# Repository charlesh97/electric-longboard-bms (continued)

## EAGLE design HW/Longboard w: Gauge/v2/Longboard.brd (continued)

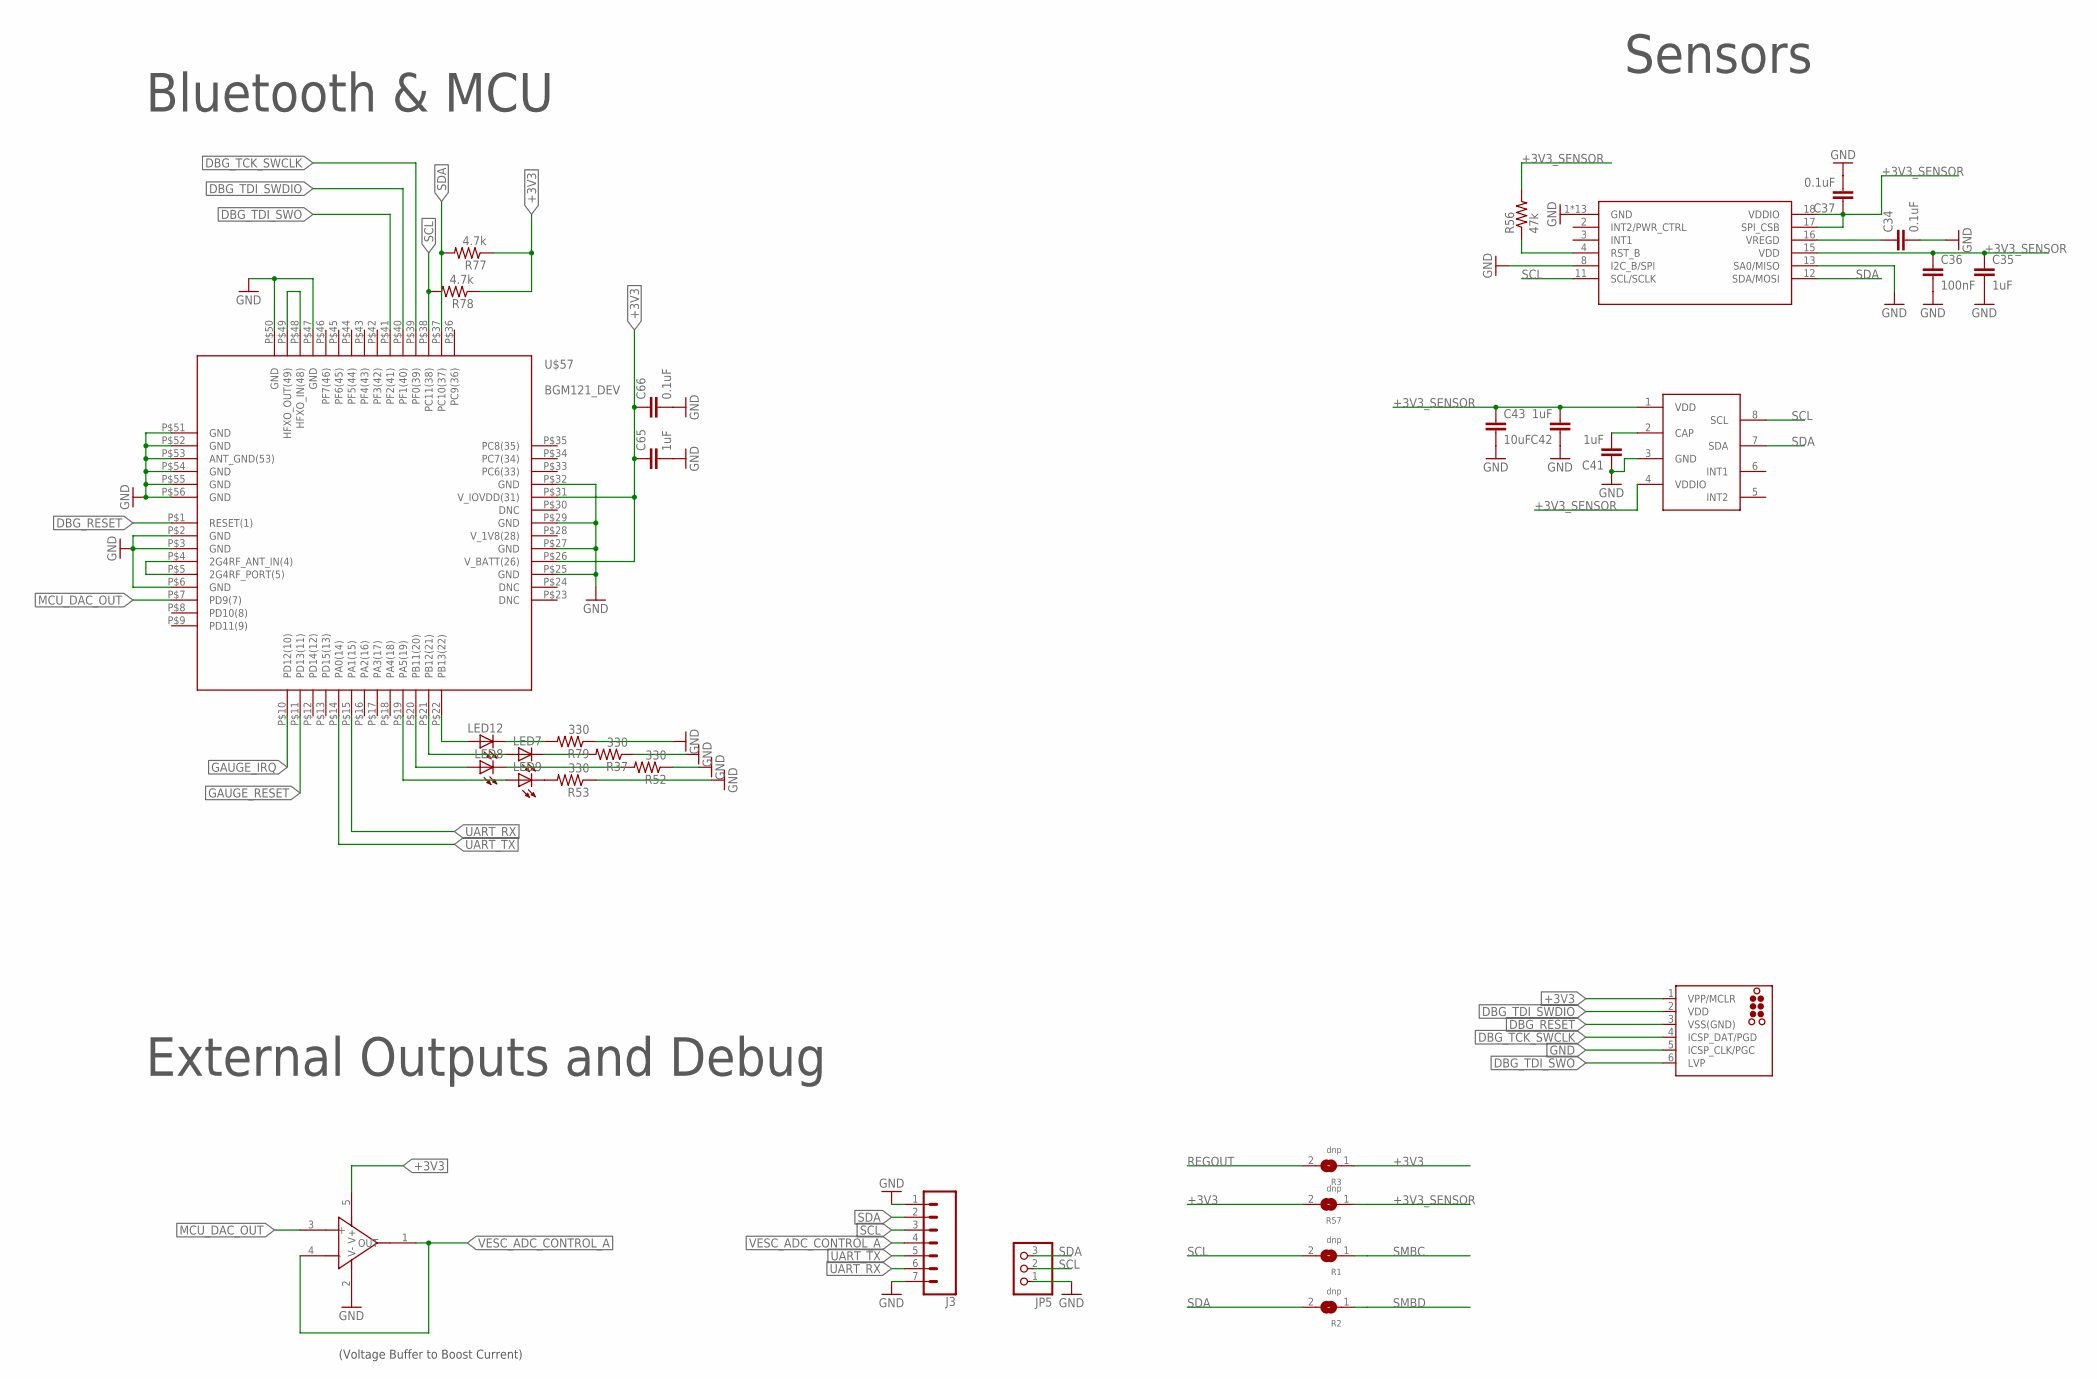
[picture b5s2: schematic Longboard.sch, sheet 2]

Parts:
C34, C37, C66: 0.1uF; C0402
C35, C41, C42, C65: 1uF; C0402
C36: 100nF; C0402
C43: 10uF; C0603
J2: TC2030-MCP-NL
J3: CONN_07; 1X07
JP5: PINHD-1X3; 1X03
LED7, LED8, LED9, LED12: LEDCHIP-LED0603; CHIP-LED0603
R1, R2, R3, R57: dnp; SOLDERJUMPER_ARROW_NOPASTE
R37, R52, R53, R79: 330; R0402
R56: 47k; R0402
R77, R78: 4.7k; R0402
U$5: MCP6001; SOT23-5L
U$25: MLP3115A2
U$34: FXAS21002
U$57: BGM121_DEV; BGM121_PAC

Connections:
+3V3: C65.1, C66.1, J2.1 (VPP/MCLR), R3.1, R57.2, R77.1, R78.1, U$5.5 (V+), U$57.P$26 (V_BATT(26)), U$57.P$31 (V_IOVDD(31))
+3V3_SENSOR: C35.1, C36.1, C37.1, C42.2, C43.1, R56.2, R57.1, U$25.1 (VDD), U$25.4 (VDDIO), U$34.15 (VDD), U$34.17 (SPI_CSB), U$34.18 (VDDIO)
DBG_RESET: J2.3 (VSS(GND)), U$57.P$1 (RESET(1))
DBG_TCK_SWCLK: J2.4 (ICSP_DAT/PGD), U$57.P$39 (PF0(39))
DBG_TDI_SWDIO: J2.2 (VDD), U$57.P$40 (PF1(40))
DBG_TDI_SWO: J2.6 (LVP), U$57.P$41 (PF2(41))
GAUGE_IRQ: U$57.P$10 (PD12(10)); also elsewhere on the board
GAUGE_RESET: U$57.P$11 (PD13(11)); also elsewhere on the board
GND: C34.2, C35.2, C36.2, C37.2, C41.1, C42.1, C43.2, C65.2, C66.2, J2.5 (ICSP_CLK/PGC), J3.1, J3.7, JP5.1, R37.1, R52.1, R53.1, R79.1, U$5.2 (V-), U$25.3 (GND), U$34.1 (GND), U$34.5 (GND), U$34.6 (GND), U$34.7 (GND), U$34.9 (GND), U$34.10 (GND), U$34.13 (SA0/MISO), U$34.14 (GND), U$34.19 (GND), U$34.20 (GND), U$34.21 (GND), U$34.22 (GND), U$34.23 (GND), U$34.24 (GND), U$57.P$2 (GND), U$57.P$3 (GND), U$57.P$6 (GND), U$57.P$25 (GND), U$57.P$27 (GND), U$57.P$29 (GND), U$57.P$32 (GND), U$57.P$47 (GND), U$57.P$50 (GND), U$57.P$51 (GND), U$57.P$52 (GND), U$57.P$53 (ANT_GND(53)), U$57.P$54 (GND), U$57.P$55 (GND), U$57.P$56 (GND); also elsewhere on the board
MCU_DAC_OUT: U$5.3 (+), U$57.P$7 (PD9(7))
unnamed: LED12.A, U$57.P$22 (PB13(22))
unnamed: LED7.A, U$57.P$21 (PB12(21))
unnamed: LED8.A, U$57.P$20 (PB11(20))
unnamed: LED9.A, U$57.P$19 (PA5(19))
unnamed: R56.1, U$34.4 (RST_B)
unnamed: LED7.C, R37.2
unnamed: LED8.C, R52.2
unnamed: LED9.C, R53.2
unnamed: C34.1, U$34.16 (VREGD)
unnamed: C41.2, U$25.2 (CAP)
unnamed: U$57.P$4 (2G4RF_ANT_IN(4)), U$57.P$5 (2G4RF_PORT(5))
unnamed: LED12.C, R79.2
unnamed: U$57.P$48 (HFXO_IN(48)), U$57.P$49 (HFXO_OUT(49))
REGOUT: R3.2; also elsewhere on the board
SCL: J3.3, JP5.2, R1.2, R78.2, U$25.8 (SCL), U$34.11 (SCL/SCLK), U$57.P$38 (PC11(38))
SDA: J3.2, JP5.3, R2.2, R77.2, U$25.7 (SDA), U$34.12 (SDA/MOSI), U$57.P$37 (PC10(37))
SMBC: R1.1; also elsewhere on the board
SMBD: R2.1; also elsewhere on the board
UART_RX: J3.6, U$57.P$15 (PA1(15))
UART_TX: J3.5, U$57.P$14 (PA0(14))
VESC_ADC_CONTROL_A: J3.4, U$5.1 (OUT), U$5.4 (-)
V_1V8(28): U$57.P$28 (V_1V8(28))

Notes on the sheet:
Bluetooth & MCU
Sensors
External Outputs and Debug
(Voltage Buffer to Boost Current)

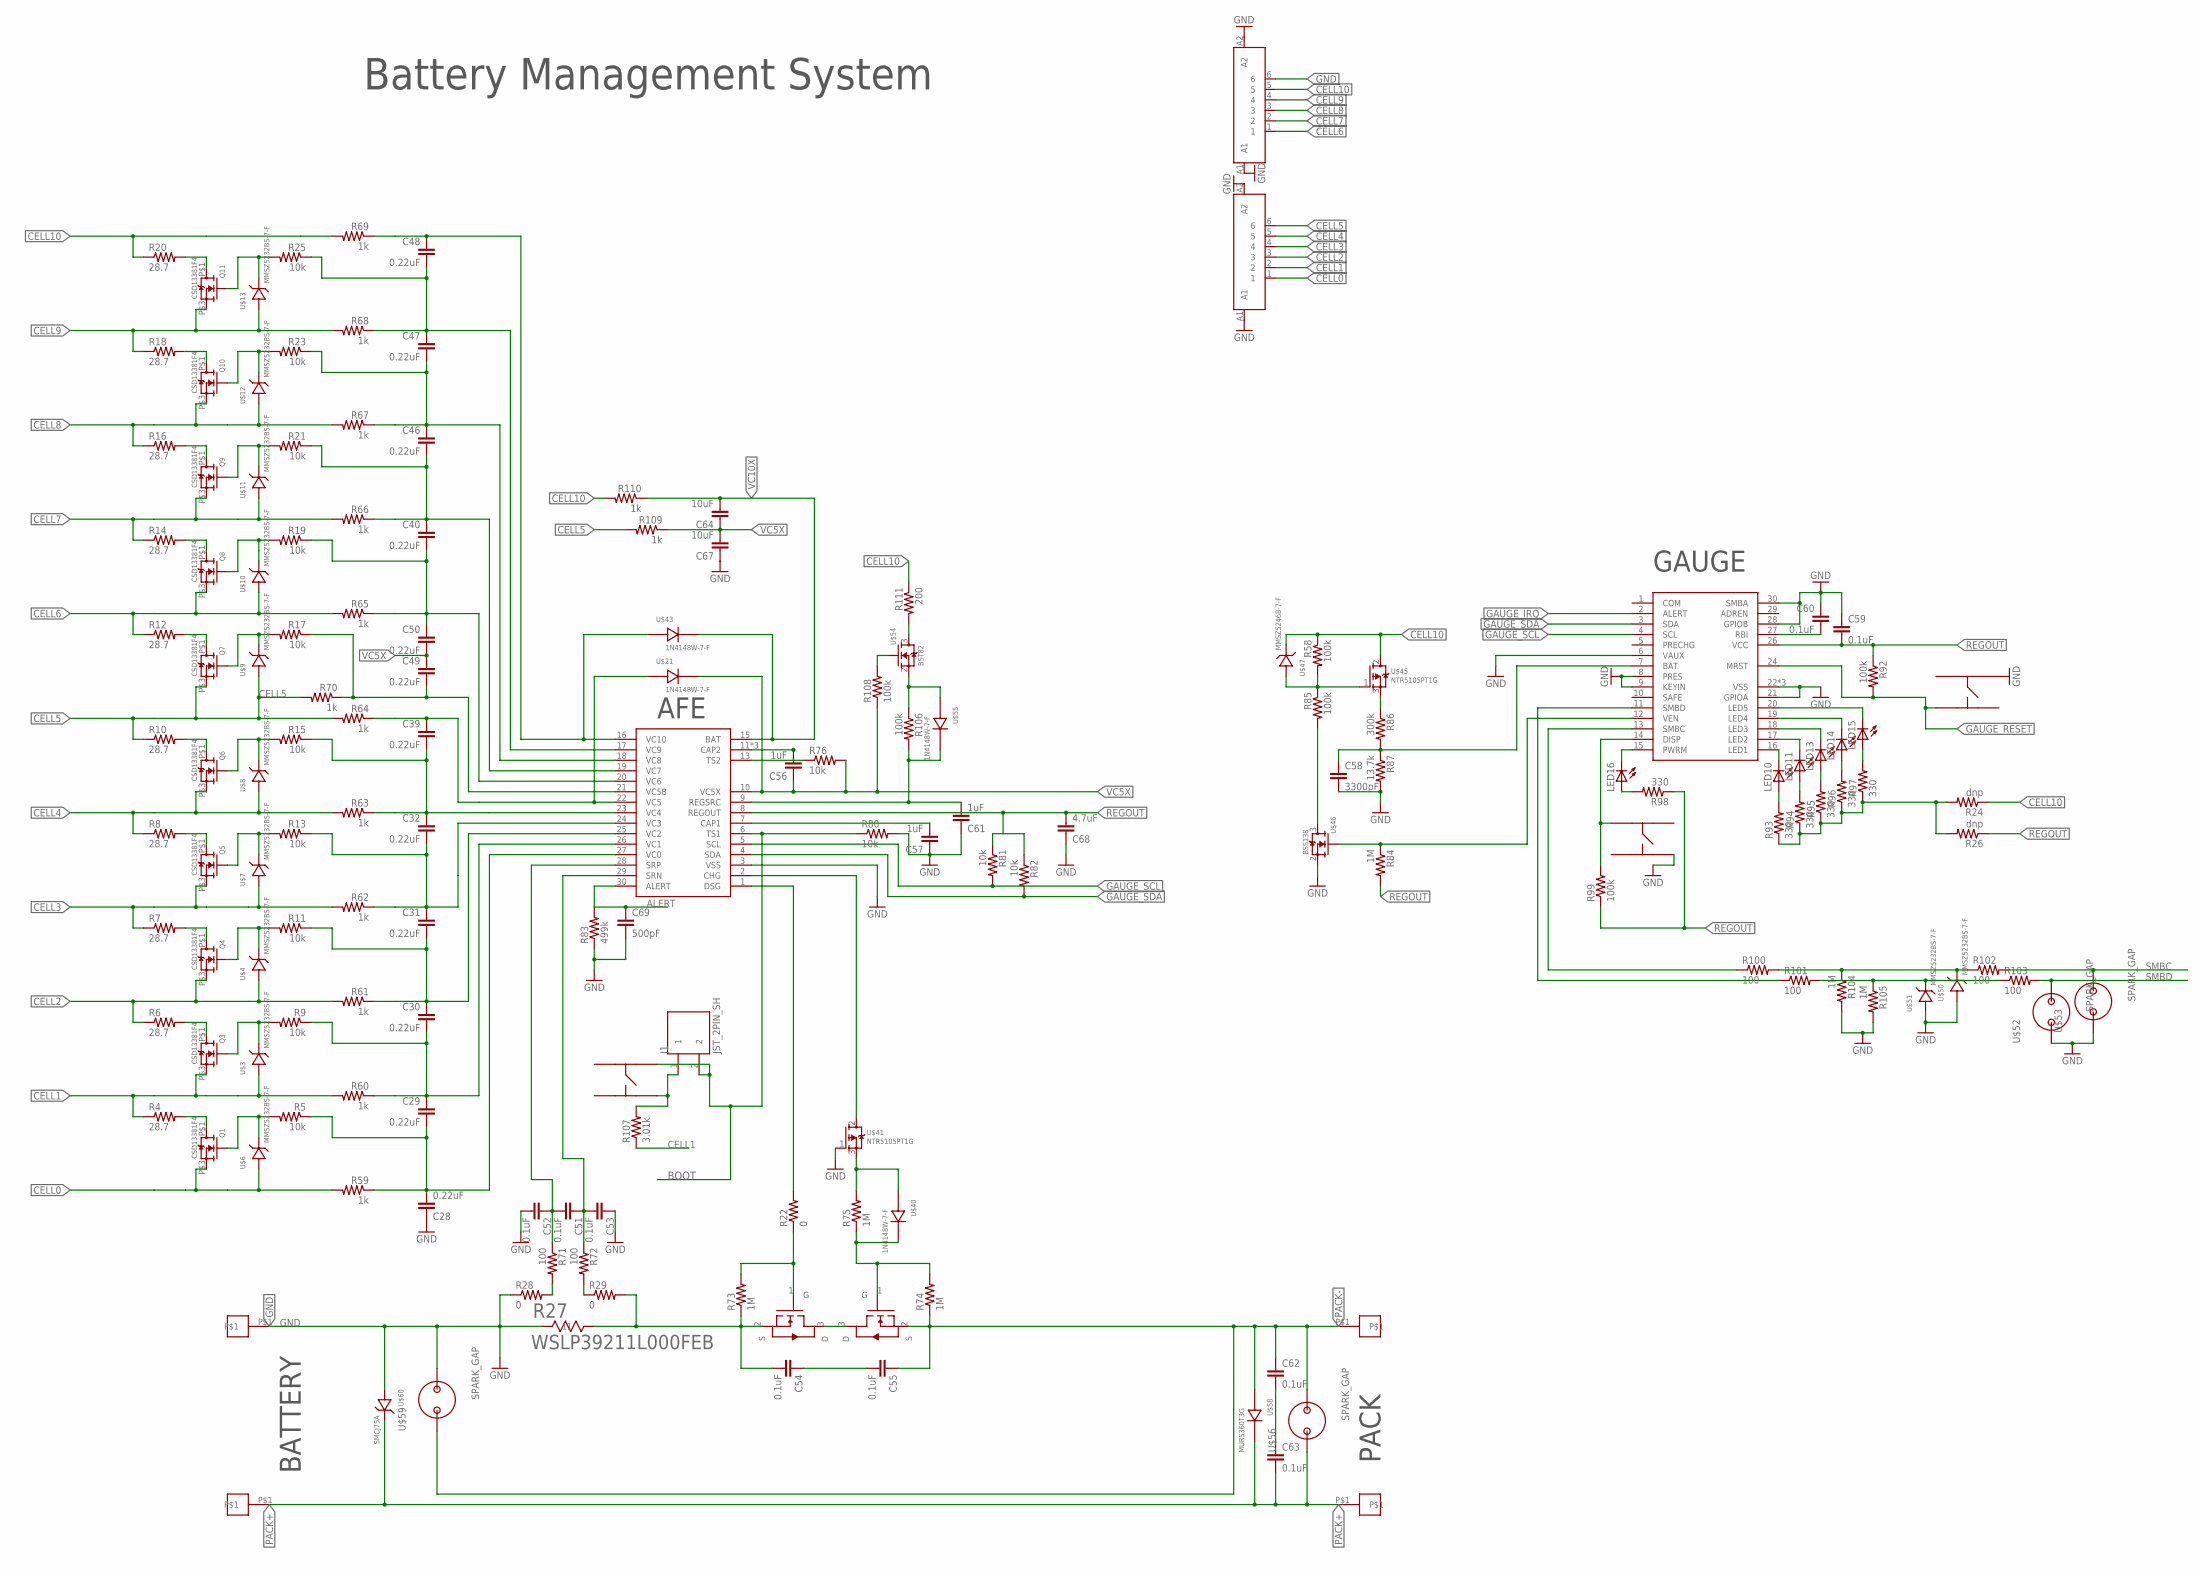
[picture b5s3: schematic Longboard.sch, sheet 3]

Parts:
C28, C29, C30, C31, C32, C39, C40, C46, C47, C48, C49, C50: 0.22uF; C0805
C51, C52, C53, C54, C55, C59, C60, C62, C63: 0.1uF; C0805
C56, C57, C61: 1uF; C0805
C58: 3300pF; C0402
C64, C67: 10uF; C1210
C68: 4.7uF; C0805
C69: 500pF; C0603
J1: JST_2PIN_SH
LED10, LED11, LED13, LED14, LED15, LED16: LEDCHIPLED_0603; CHIPLED_0603
Q1, Q3, Q4, Q5, Q6, Q7, Q8, Q9, Q10, Q11: CSD13381F4; 3-XFDFN
R4, R6, R7, R8, R10, R12, R14, R16, R18, R20: 28.7; R2010
R5, R9, R11, R13, R15, R17, R19, R21, R23, R25: 10k; R1206
R22: 0; R1206
R24, R26: dnp; R0402
R27: WSLP39211L000FEB; W-3921
R28, R29: 0; R0402
R58, R85, R92, R106, R108: 100k; R0805
R59, R60, R61, R62, R63, R64, R65, R66, R67, R68, R69, R70, R109, R110: 1k; R1206
R71, R72, R100, R101, R102, R103: 100; R0805
R73, R74, R75, R84, R104, R105: 1M; R1206
R76, R80, R81, R82: 10k; R0805
R83: 499k; R0603
R86: 300k; R0805
R87: 13.7k; R0805
R93, R94, R95, R96, R97, R98: 330; R0402
R99: 100k; R0402
R107: 3.01k; R1206
R111: 200; R1206
S1, S2, S3: KMR731NG
U$3, U$4, U$6, U$7, U$8, U$9, U$10, U$11, U$12, U$13, U$50, U$51: MMSZ5232BS-7-F; SOD-323F
U$14, U$15, U$16, U$17: PAD
U$18, U$19: JST_6PIN
U$20: BQ76930; SOIC-30
U$21, U$40, U$43, U$55: 1N4148W-7-F; SOD-123
U$22, U$23: AOB290L; TO-263
U$41, U$45: NTR5105PT1G; SOT23-3
U$44: BQ78350-R1; SOIC-30
U$46: BSS138; SOT23-3
U$47: MMSZ5246B-7-F; SOD-123
U$52, U$53, U$56, U$59: SPARK_GAP
U$54: BST82; SOT23-3
U$58: MURS360T3G; SMC(DO-214AB)
U$60: SMCJ75A; SMC(DO-214AB)

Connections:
ALERT: C69.1, R83.2, U$20.30 (ALERT)
BOOT: J1.2, R80.1, S1.P$2, U$20.6 (TS1)
CELL0: Q1.P$3 (S), R59.2, U$6.1, U$19.1
CELL1: Q3.P$3 (S), R4.1, R60.2, R107.1, U$3.1, U$19.2
CELL2: Q4.P$3 (S), R6.1, R61.2, U$4.1, U$19.3
CELL3: Q5.P$3 (S), R7.1, R62.2, U$7.1, U$19.4
CELL4: Q6.P$3 (S), R8.1, R63.2, U$8.1, U$19.5
CELL5: Q7.P$3 (S), R10.1, R64.2, R70.2, R109.2, U$9.1, U$19.6
CELL6: Q8.P$3 (S), R12.1, R65.2, U$10.1, U$18.1
CELL7: Q9.P$3 (S), R14.1, R66.2, U$11.1, U$18.2
CELL8: Q10.P$3 (S), R16.1, R67.2, U$12.1, U$18.3
CELL9: Q11.P$3 (S), R18.1, R68.2, U$13.1, U$18.4
CELL10: R20.1, R24.1, R58.1, R69.2, R110.2, R111.1, U$18.5, U$45.2 (S), U$47.P$2 (2)
GAUGE_IRQ: U$44.2 (ALERT); also elsewhere on the board
GAUGE_RESET: R92.2, S3.P$4, U$44.24 (MRST); also elsewhere on the board
GAUGE_SCL: R81.2, U$20.5 (SCL), U$44.4 (SCL)
GAUGE_SDA: R82.2, U$20.4 (SDA), U$44.3 (SDA)
GND: C28.1, C52.2, C53.1, C57.1, C58.2, C59.1, C60.1, C61.1, C67.1, C68.1, C69.2, R27.1 (11), R28.1, R80.2, R83.1, R87.2, R104.2, R105.2, S2.P$3, S3.P$2, U$17.P$1, U$18.6, U$18.A1, U$18.A2, U$19.A1, U$19.A2, U$20.3 (VSS), U$41.1 (G), U$44.6 (VAUX), U$44.8 (PRES), U$44.9 (KEYIN), U$44.21 (GPIOA), U$44.22 (VSS), U$44.23 (VSS), U$44.25 (VSS), U$44.28 (GPIOB), U$44.30 (SMBA), U$46.2 (S), U$50.1, U$51.1, U$52.P$1, U$53.P$1, U$59.P$2, U$60.1; also elsewhere on the board
unnamed: R28.2, R71.2
unnamed: R29.1, R72.2
unnamed: Q1.P$1 (D), R4.2
unnamed: Q8.P$2 (G), R19.2, U$10.2
unnamed: Q1.P$2 (G), R5.2, U$6.2
unnamed: Q3.P$1 (D), R6.2
unnamed: Q3.P$2 (G), R9.2, U$3.2
unnamed: R22.2, U$20.1 (DSG)
unnamed: Q5.P$1 (D), R8.2
unnamed: Q4.P$1 (D), R7.2
unnamed: Q4.P$2 (G), R11.2, U$4.2
unnamed: Q5.P$2 (G), R13.2, U$7.2
unnamed: Q6.P$2 (G), R15.2, U$8.2
unnamed: Q8.P$1 (D), R14.2
unnamed: C40.2, C50.1, R19.1, R65.1, U$20.20 (VC6)
unnamed: C49.2, R17.1, R70.1, U$20.21 (VC5B)
unnamed: R24.2, R26.2, R93.1, R94.1, R95.1, R96.1, R97.1
unnamed: Q6.P$1 (D), R10.2
unnamed: Q7.P$1 (D), R12.2
unnamed: Q7.P$2 (G), R17.2, U$9.2
unnamed: Q9.P$1 (D), R16.2
unnamed: Q10.P$1 (D), R18.2
unnamed: Q11.P$1 (D), R20.2
unnamed: Q11.P$2 (G), R25.2, U$13.2
unnamed: Q10.P$2 (G), R23.2, U$12.2
unnamed: Q9.P$2 (G), R21.2, U$11.2
unnamed: C29.1, C30.2, R9.1, R60.1, U$20.26 (VC1)
unnamed: C30.1, C31.2, R11.1, R61.1, U$20.25 (VC2)
unnamed: C31.1, C32.2, R13.1, R62.1, U$20.24 (VC3)
unnamed: C32.1, C39.2, R15.1, R63.1, U$20.23 (VC4)
unnamed: C39.1, R64.1, U$20.22 (VC5), U$21.P$1
unnamed: C40.1, C46.2, R21.1, R66.1, U$20.19 (VC7)
unnamed: C46.1, C47.2, R23.1, R67.1, U$20.18 (VC8)
unnamed: C47.1, C48.2, R25.1, R68.1, U$20.17 (VC9)
unnamed: C48.1, R69.1, U$20.16 (VC10), U$43.P$1
unnamed: C28.2, C29.2, R5.1, R59.1, U$20.27 (VC0)
unnamed: C51.1, C53.2, R72.1, U$20.29 (SRN)
unnamed: C51.2, C52.1, R71.1, U$20.28 (SRP)
unnamed: C54.2, R27.2 (22), R29.2, R73.1, U$22.2 (S)
unnamed: U$22.3 (D), U$23.3 (D)
unnamed: R74.2, R75.1, U$23.1 (G), U$40.P$2
unnamed: R75.2, U$40.P$1, U$41.3 (D)
unnamed: U$20.2 (CHG), U$41.2 (S)
unnamed: C54.1, C55.2
unnamed: C56.2, U$20.11 (CAP2), U$20.12 (CAP2), U$20.14 (CAP2)
unnamed: R76.1, U$20.13 (TS2)
unnamed: C57.2, U$20.7 (CAP1)
unnamed: R84.1, U$44.12 (VEN), U$46.1 (G)
unnamed: R85.2, U$46.3 (D)
unnamed: R58.2, R85.1, U$45.1 (G), U$47.P$1 (1)
unnamed: R86.1, U$45.3 (D)
unnamed: C58.1, R86.2, R87.1, U$44.7 (BAT)
unnamed: C60.2, U$44.27 (RBI)
unnamed: LED10.A, R93.2
unnamed: LED11.A, R94.2
unnamed: LED13.A, R95.2
unnamed: LED14.A, R96.2
unnamed: LED15.A, R97.2
unnamed: LED10.C, U$44.16 (LED1)
unnamed: LED11.C, U$44.17 (LED2)
unnamed: LED13.C, U$44.18 (LED3)
unnamed: LED14.C, U$44.19 (LED4)
unnamed: LED15.C, U$44.20 (LED5)
unnamed: LED16.A, R98.2
unnamed: R99.2, S2.P$1, U$44.14 (DISP)
unnamed: LED16.C, U$44.15 (PWRM)
unnamed: R101.1, U$44.11 (SMBD)
unnamed: R100.1, U$44.13 (SMBC)
unnamed: R100.2, R102.1, R104.1, U$50.2
unnamed: R101.2, R103.1, R105.1, U$51.2
unnamed: R106.1, U$54.2 (S), U$55.P$1
unnamed: R111.2, U$54.3 (D)
unnamed: R22.1, R73.2, U$22.1 (G)
unnamed: J1.1, R107.2, S1.P$3
unnamed: C62.2, C63.1
unnamed: R108.2, U$54.1 (G)
PACK+: C63.2, U$15.P$1, U$16.P$1, U$56.P$1, U$58.2, U$60.2
PACK-: C55.1, C62.1, R74.1, U$14.P$1, U$23.2 (S), U$56.P$2, U$58.1, U$59.P$1
REGOUT: C59.2, C68.2, R26.1, R81.1, R82.1, R84.2, R92.1, R98.1, R99.1, U$20.8 (REGOUT), U$44.26 (VCC); also elsewhere on the board
REGSRC: C61.2, R106.2, U$20.9 (REGSRC), U$55.P$2
SMBC: R102.2, U$53.P$2; also elsewhere on the board
SMBD: R103.2, U$52.P$2; also elsewhere on the board
VC5X: C49.1, C50.2, C56.1, C64.1, C67.2, R76.2, R108.1, R109.1, U$20.10 (VC5X), U$21.P$2
VC10X: C64.2, R110.1, U$20.15 (BAT), U$43.P$2

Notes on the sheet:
BATTERY
PACK
GAUGE
AFE
Battery Management System

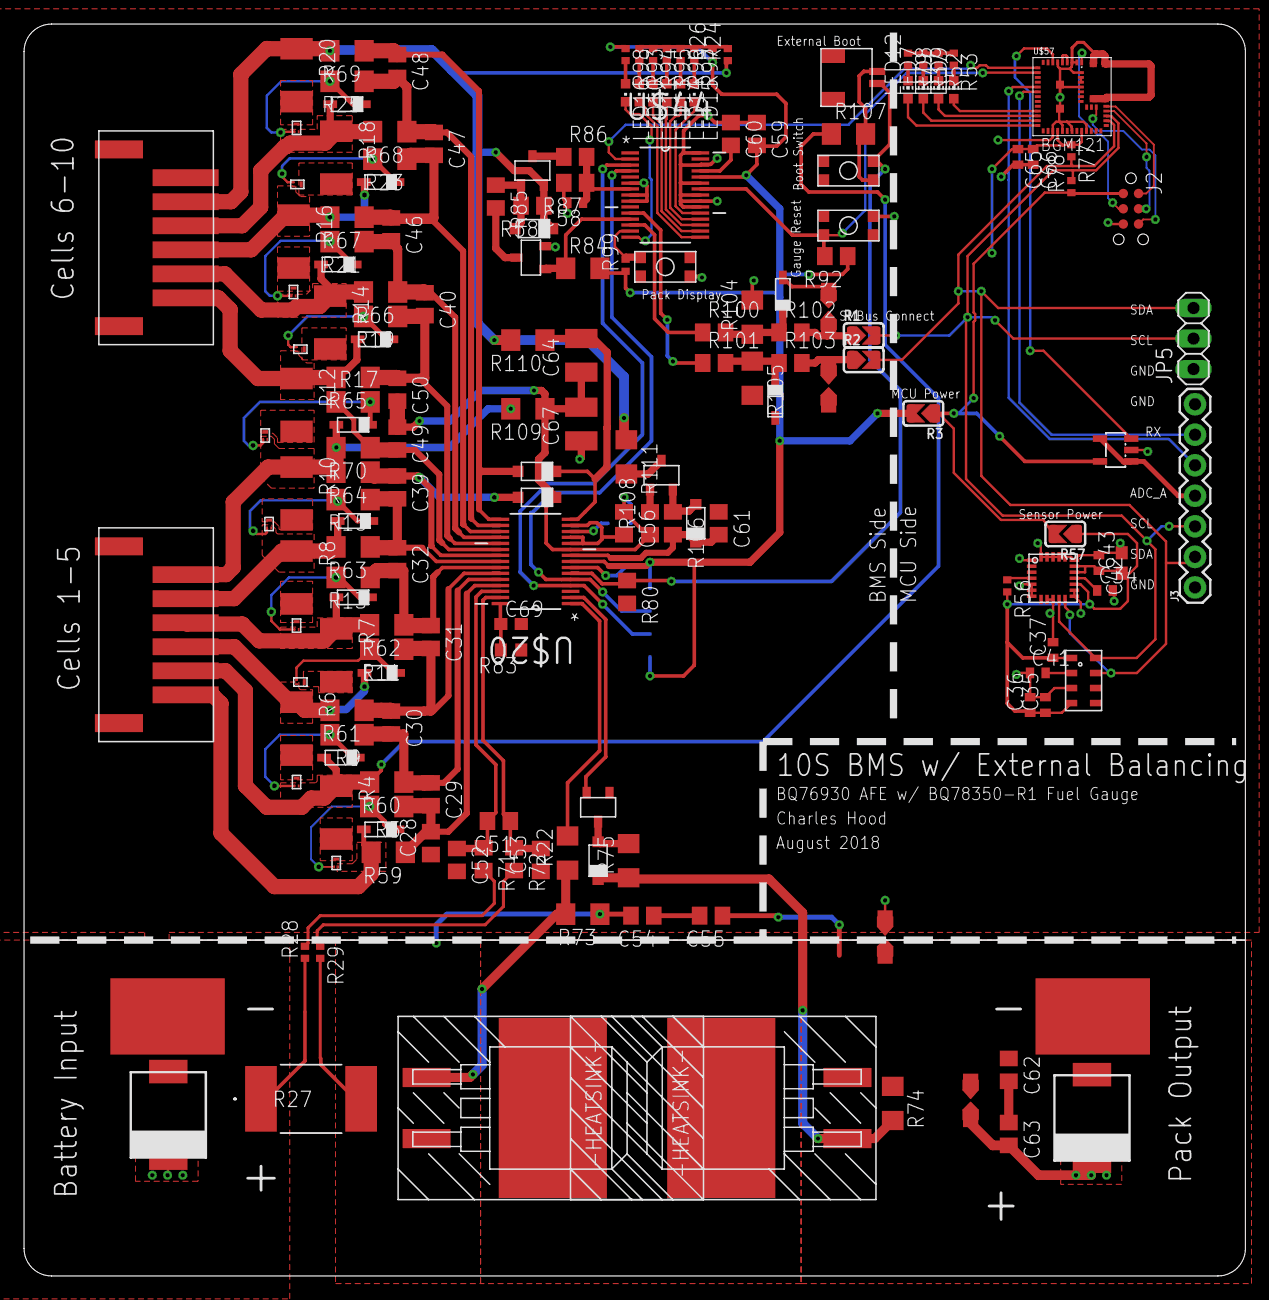
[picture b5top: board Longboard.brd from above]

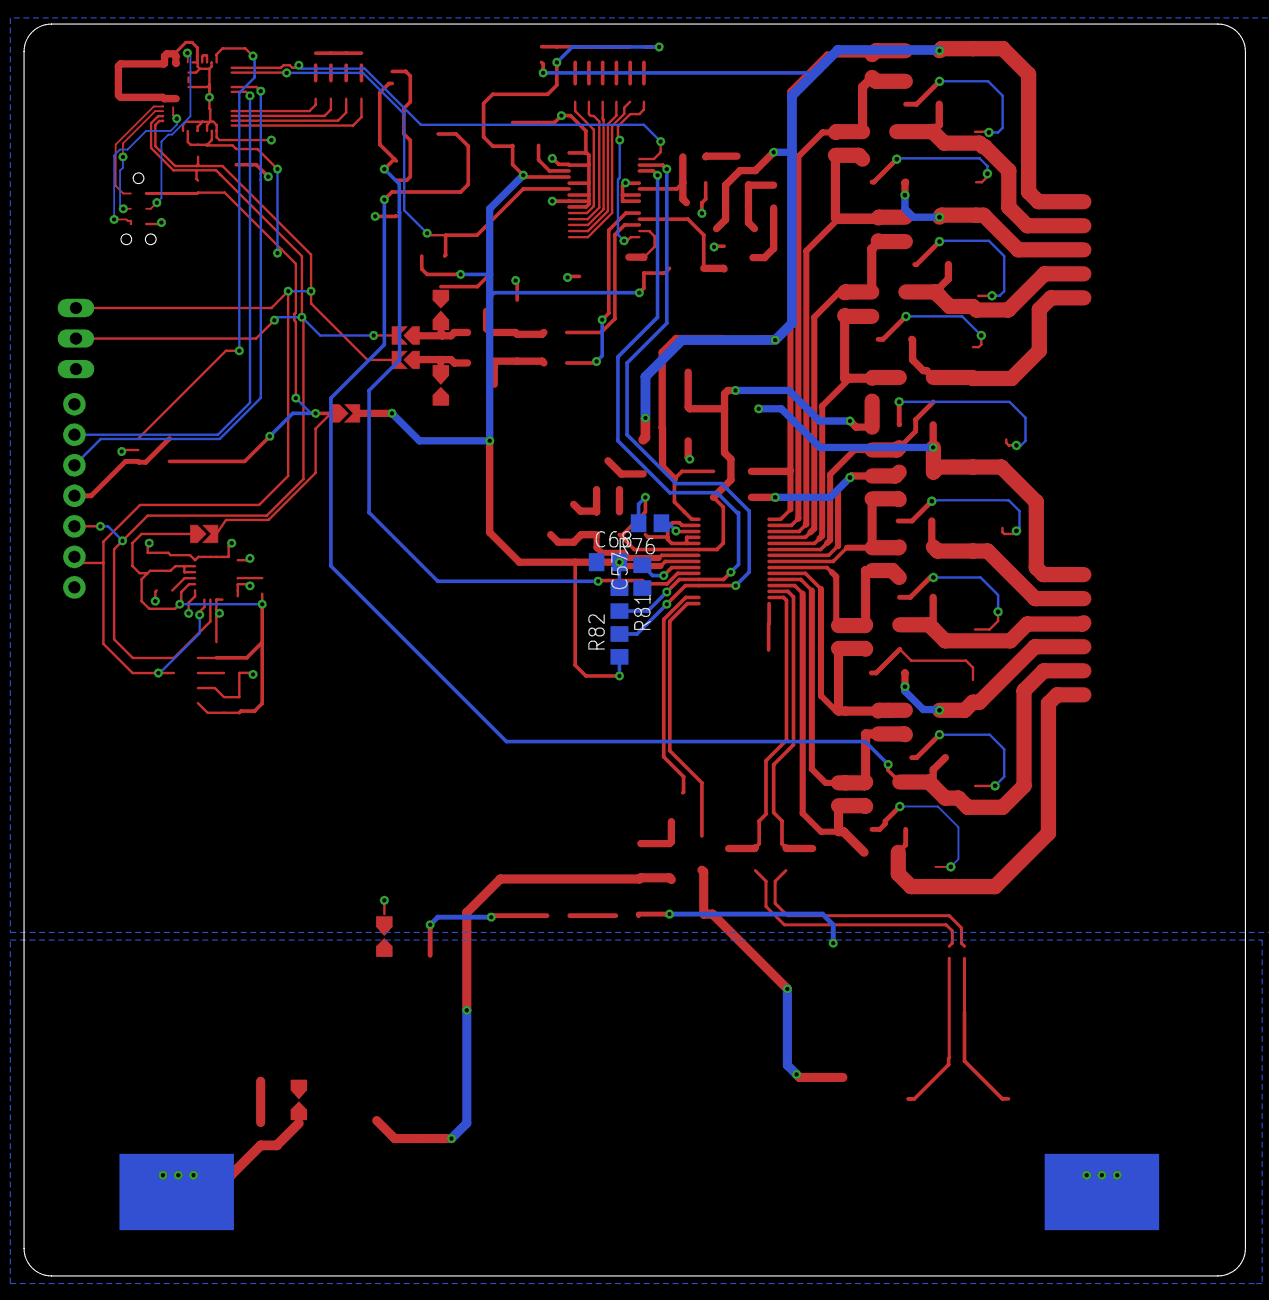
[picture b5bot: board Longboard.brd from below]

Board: 2 copper layers, 101.6 x 104.1 mm, 190 parts (7 on the bottom side), 127 nets.

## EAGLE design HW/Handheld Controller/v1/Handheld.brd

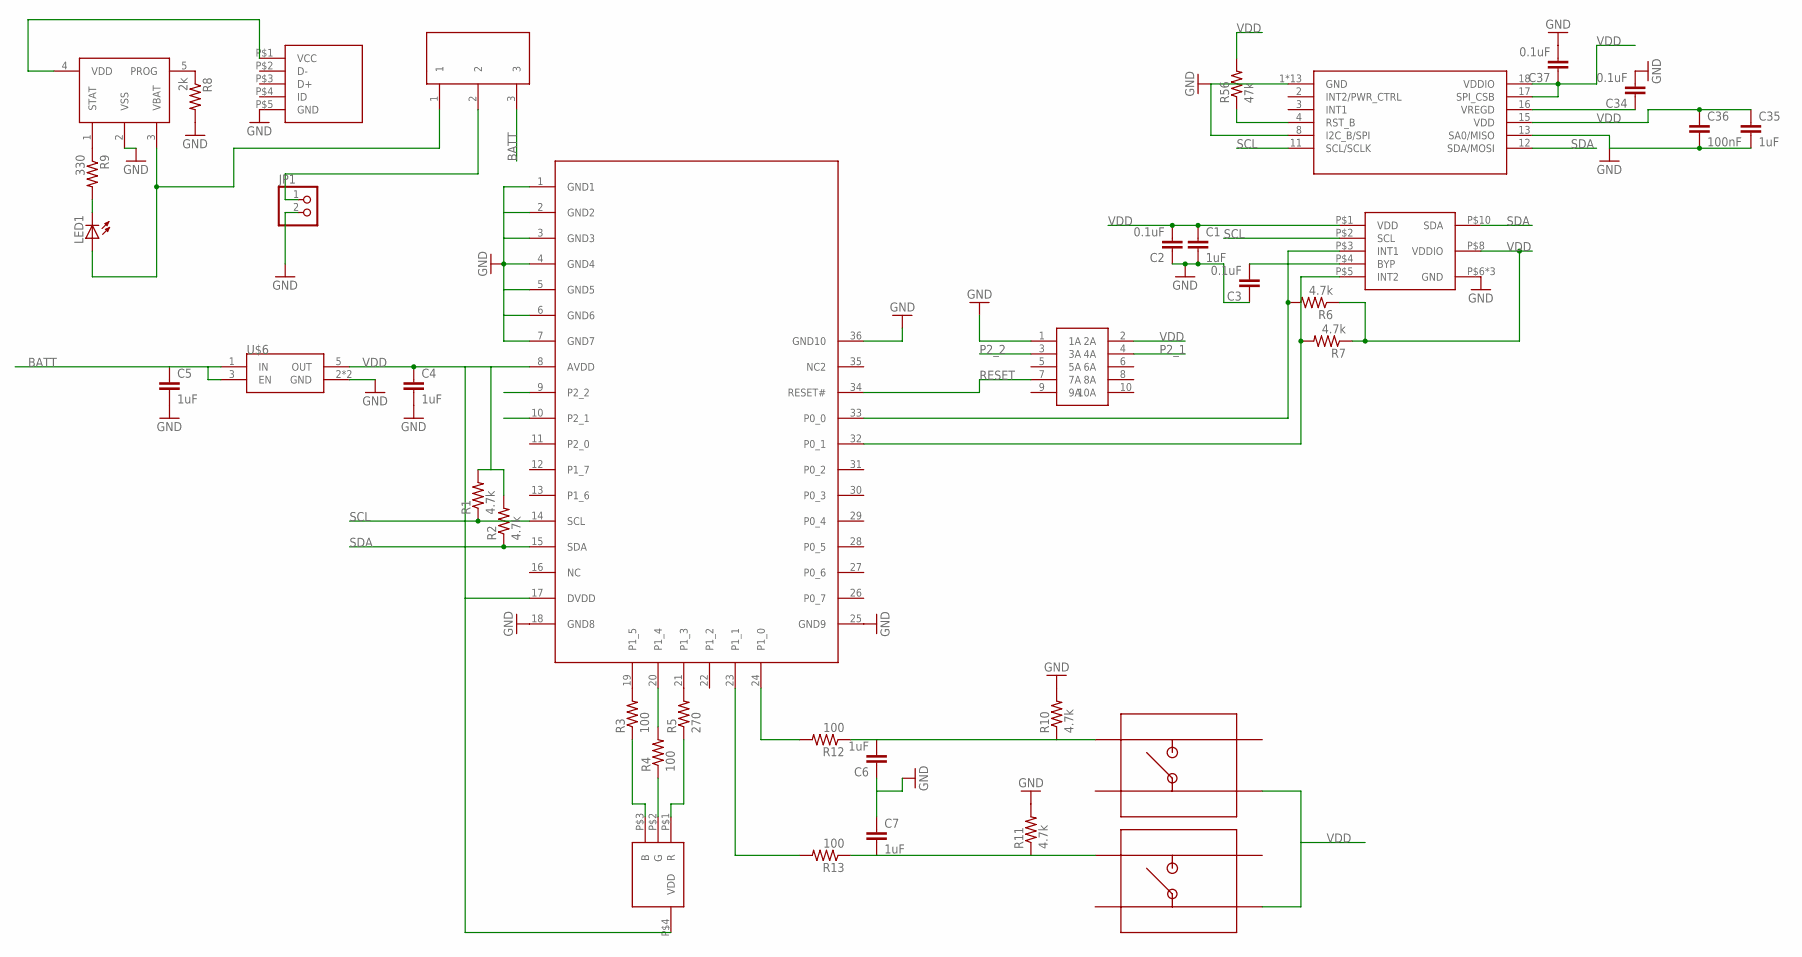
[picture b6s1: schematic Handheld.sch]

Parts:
C1, C4, C5, C6, C7, C35: 1uF; C0402
C2, C3, C34, C37: 0.1uF; C0402
C36: 100nF; C0402
JP1: PINHD-1X2; 1X02
LED1: LEDCHIPLED_0805; CHIPLED_0805
R1, R2, R6, R7, R10, R11: 4.7k; R0402
R3, R4, R12, R13: 100; R0402
R5: 270; R0402
R8: 2k; R0402
R9: 330; R0402
R56: 47k; R0402
U$1: BLE113; BLUEGIGA
U$2: RIBBON_10POS_MALE
U$3: MMA8653FC; 10-DFN2X2
U$4: MCP73831
U$5: MICRO_USB; MOLEX_USB
U$6: TPS782XX; SOT23-5L
U$7: LTST-C19HE1WT
U$8, U$9: SMD_TACTILE; EVQ-Q2U03W
U$10: SPDT_THRU
U$34: FXAS21002

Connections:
BATT: C5.1, U$6.1 (IN), U$6.3 (EN), U$10.3
GND: C1.2, C2.1, C3.1, C4.2, C5.2, C6.1, C7.1, C34.2, C35.2, C36.2, C37.2, JP1.2, R8.2, R10.2, R11.2, U$1.1 (GND1), U$1.2 (GND2), U$1.3 (GND3), U$1.4 (GND4), U$1.5 (GND5), U$1.6 (GND6), U$1.7 (GND7), U$1.18 (GND8), U$1.25 (GND9), U$1.36 (GND10), U$2.1 (1A), U$3.P$6 (GND), U$3.P$7 (GND), U$3.P$9 (GND), U$4.2 (VSS), U$5.P$5 (GND), U$6.2 (GND), U$6.4 (GND), U$34.1 (GND), U$34.5 (GND), U$34.6 (GND), U$34.7 (GND), U$34.8 (I2C_B/SPI), U$34.9 (GND), U$34.10 (GND), U$34.13 (SA0/MISO), U$34.14 (GND), U$34.19 (GND), U$34.20 (GND), U$34.21 (GND), U$34.22 (GND), U$34.23 (GND), U$34.24 (GND)
unnamed: C7.2, R11.1, R13.1, U$9.1
unnamed: R3.2, U$1.19 (P1_5)
unnamed: C3.2, U$3.P$4 (BYP)
unnamed: R4.2, U$1.20 (P1_4)
unnamed: R5.2, U$1.21 (P1_3)
unnamed: R3.1, U$7.P$3 (B)
unnamed: R4.1, U$7.P$2 (G)
unnamed: R5.1, U$7.P$1 (R)
unnamed: R6.2, U$1.33 (P0_0), U$3.P$3 (INT1)
unnamed: R7.2, U$1.32 (P0_1), U$3.P$5 (INT2)
unnamed: R8.1, U$4.5 (PROG)
unnamed: R9.1, U$4.1 (STAT)
unnamed: LED1.C, R9.2
unnamed: LED1.A, U$4.3 (VBAT), U$10.1
unnamed: U$4.4 (VDD), U$5.P$1 (VCC)
unnamed: JP1.1, U$10.2
unnamed: R13.2, U$1.23 (P1_1)
unnamed: R12.2, U$1.24 (P1_0)
unnamed: C6.2, R10.1, R12.1, U$8.1
unnamed: R56.1, U$34.4 (RST_B)
unnamed: C34.1, U$34.16 (VREGD)
P2_1: U$2.4 (4A)
P2_2: U$2.3 (3A)
RESET: U$1.34 (RESET#), U$2.7 (7A)
SCL: R1.1, U$1.14 (SCL), U$3.P$2 (SCL), U$34.11 (SCL/SCLK)
SDA: R2.1, U$1.15 (SDA), U$3.P$10 (SDA), U$34.12 (SDA/MOSI)
VDD: C1.1, C2.2, C4.1, C35.1, C36.1, C37.1, R1.2, R2.2, R6.1, R7.1, R56.2, U$1.8 (AVDD), U$1.17 (DVDD), U$2.2 (2A), U$3.P$1 (VDD), U$3.P$8 (VDDIO), U$6.5 (OUT), U$7.P$4 (VDD), U$8.4, U$9.4, U$34.15 (VDD), U$34.17 (SPI_CSB), U$34.18 (VDDIO)

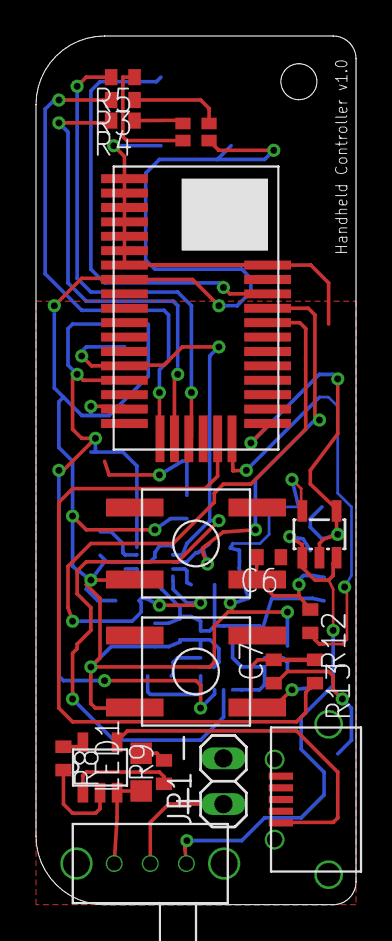
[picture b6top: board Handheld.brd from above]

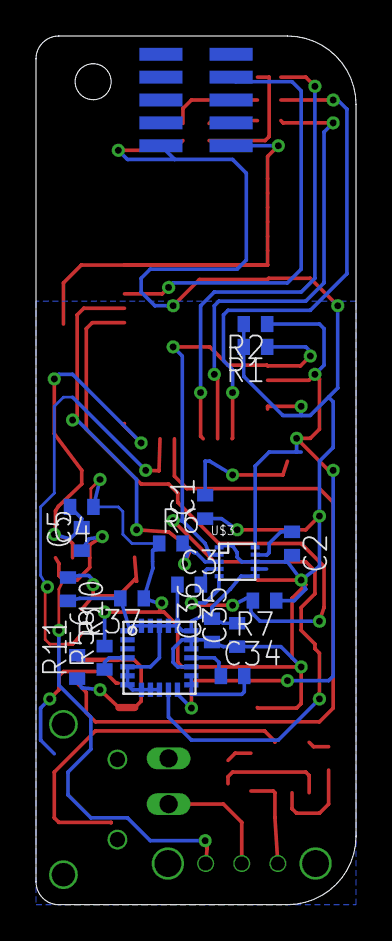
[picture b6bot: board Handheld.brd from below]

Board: 2 copper layers, 17.8 x 48.3 mm, 38 parts (19 on the bottom side), 27 nets.
